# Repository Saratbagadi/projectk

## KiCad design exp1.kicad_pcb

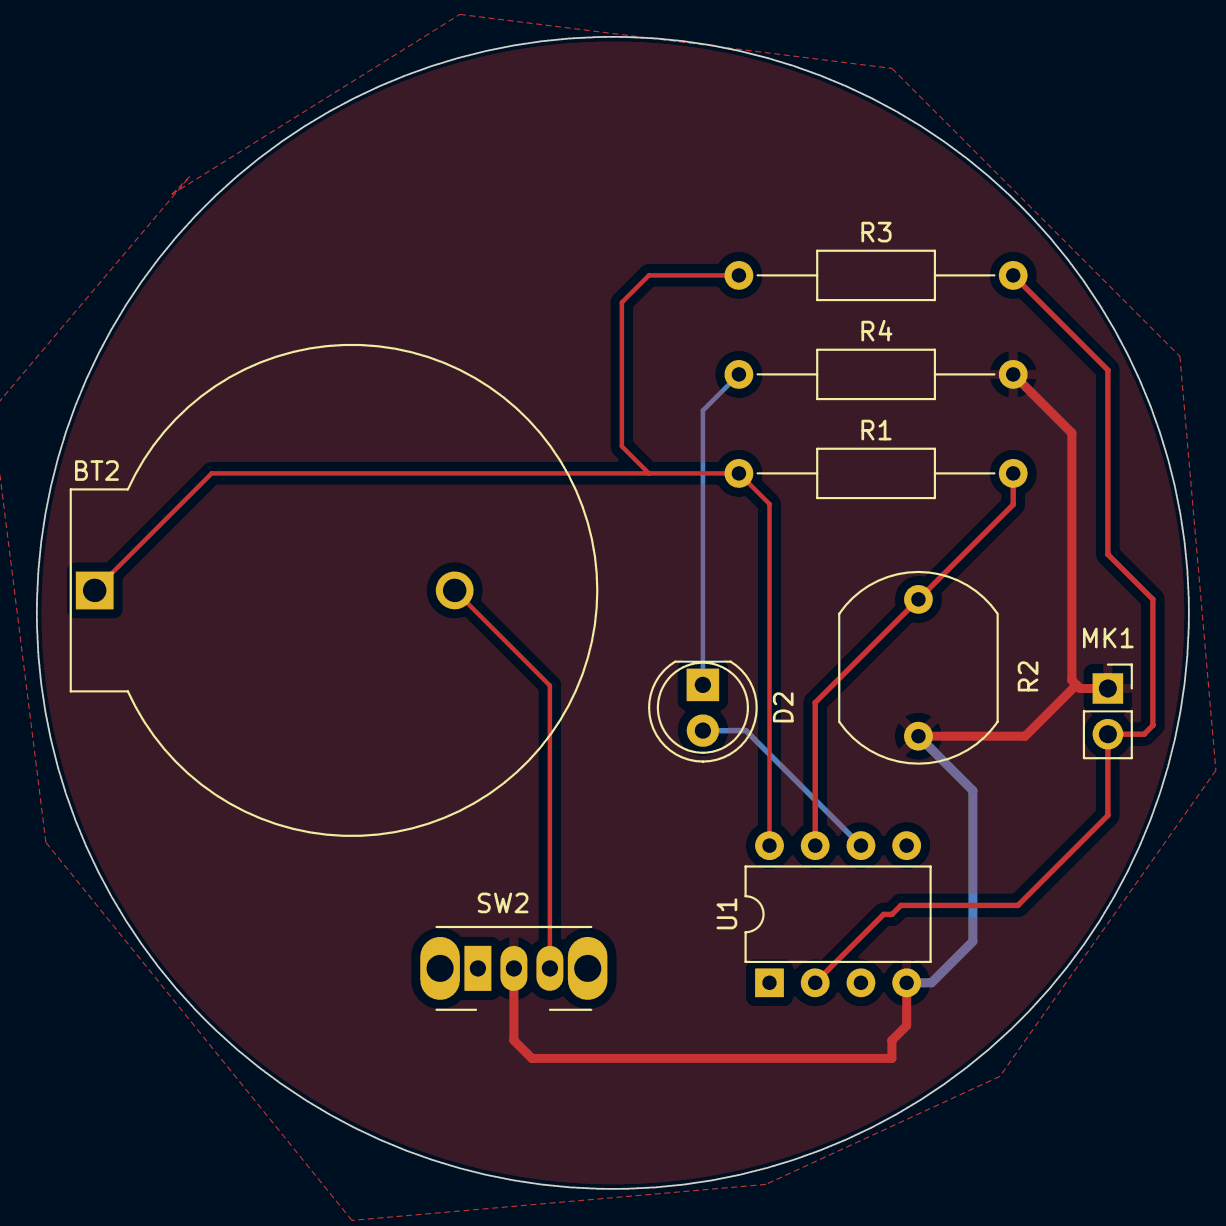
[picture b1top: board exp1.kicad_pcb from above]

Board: 2 copper layers, 64.0 x 64.0 mm, 9 parts (0 on the bottom side), 7 nets.

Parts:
BT2: 3.3v Cell; BatteryHolder_ComfortableElectronic_CH273-2450_1x2450
D2: 5mm Yellow LED; LED_D5.0mm
MK1: Microphone_Condenser; PinSocket_1x02_P2.54mm_Vertical
R1: 10k; R_Axial_DIN0207_L6.3mm_D2.5mm_P15.24mm_Horizontal
R2: 5mm LDR; R_LDR_10x8.5mm_P7.6mm_Vertical
R3: 5.6k; R_Axial_DIN0207_L6.3mm_D2.5mm_P15.24mm_Horizontal
R4: 470R; R_Axial_DIN0207_L6.3mm_D2.5mm_P15.24mm_Horizontal
SW2: SW_SPDT; SW_Slide_SPDT_Angled_CK_OS102011MA1Q
U1: ATtiny85V-10P; DIP-8_W7.62mm

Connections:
+3.3V: BT2.1 (+), R1.1, R3.1, U1.8 (VCC)
/LDR: R1.2, R2.1, U1.7 (PB2)
/LED: D2.2 (A), U1.6 (PB1)
/MIC: MK1.2 (+), R3.2, U1.2 (XTAL1/PB3)
GND: MK1.1 (-), R2.2, R4.2, SW2.2 (B), U1.4 (GND)
unnamed: BT2.2 (-), SW2.3 (C)
unnamed: D2.1 (K), R4.1
